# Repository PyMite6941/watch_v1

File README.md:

# Watch V1

A see-through, build-it-yourself wrist watch made as a gift for STEM teachers. An ESP32-C3 SuperMini drives a four-digit LED display, an RGB LED and a vibration motor inside a clear printed case. Every watch is set up for its owner with **Watch Studio**, a tiny desktop app for Windows and macOS — no programming — and takes plug-in **packs** for extra abilities (a weather sensor for biology, a microphone tuner for music).

| | |
|---|---|
| Size | 62.8 × 48.8 × 25.3 mm case, 22 mm strap |
| Display | 0.56" four-digit seven-segment, auto-dimming |
| Battery | 150 mAh Li-Po, charged through its own USB socket |
| Radios | Wi-Fi (time sync), Bluetooth LE (setup), ESP-NOW (watch-to-watch) |
| Controls | Two buttons: MODE and SET |
| Expansion | 2×3 accessory socket on the face (I²C, switched power, analogue in) |

## Where things stand

| Part | State |
|---|---|
| Circuit (`hardware/scripts/design.py`) | Done, revision 5. Schematic generated, electrical rules check passes with 0 findings. |
| PCB | All 49 parts placed and checked; an automatic audit confirms every connection against the parts' pinouts. Routing and Gerbers are made in the cloud by a GitHub workflow, so builders never run a router — see [`hardware/README.md`](hardware/README.md). |
| Enclosure | Modelled; STL files exported in `enclosure/stl/`. Not yet test-printed against a real board. |
| Firmware 2.2.0 | Complete and compiles for the ESP32-C3 (custom apps, file space, live data, I²C bridge, weather). **Not yet run on hardware** — expect a debugging session on the first assembled watch. |
| Watch Studio app | Done; tested against its built-in demo watch. Installers for Windows (tested) and macOS (not yet tried on a Mac) in [`installer/`](installer/README.md). Needs a real watch to be tested over USB and Bluetooth. |

The list of what is left is kept outside the repository.

## Start here

| You want to… | Read |
|---|---|
| Use a finished watch | [`docs/USER_GUIDE.md`](docs/USER_GUIDE.md) |
| Install the app | Download from [Releases](https://github.com/PyMite6941/watch_v1/releases) — details in [`installer/README.md`](installer/README.md) |
| Use the app without installing it | Host it on the web with Vercel, or run it as a Java app — [`docs/APP_HOSTING.md`](docs/APP_HOSTING.md) |
| Set one up (Wi-Fi, screens, bells, custom apps) | [`docs/CONFIGURATION.md`](docs/CONFIGURATION.md) |
| Build one | [`docs/BUILD_GUIDE.md`](docs/BUILD_GUIDE.md), parts in [`docs/BOM.md`](docs/BOM.md) |
| Order boards and cases | [`docs/ORDERING.md`](docs/ORDERING.md); what each add-on costs: [`docs/COSTS.md`](docs/COSTS.md) |
| Add sensors or other hardware | [`docs/ADDONS.md`](docs/ADDONS.md); pack boards and costs in [`hardware/addons/`](hardware/addons/README.md) |
| See what it could do for each subject | [`docs/IDEAS.md`](docs/IDEAS.md) |
| Make one for a particular person (biology, computer science, band, calculus, youth group) | [`kits/`](kits/README.md): preset, pack, engraved case and printed stand for each |
| Change the circuit or board | [`hardware/README.md`](hardware/README.md) |

## What it does

- **Clock**: time, seconds, date, battery level. Keeps time with a DS3231 clock chip and corrects itself over Wi-Fi.
- **Weather** (over Wi-Fi): temperature, sky, high/low, chance of rain, sunrise/sunset and air quality for a place you choose.
- **Classroom tools**: stopwatch, countdown timer, tally counter, dice, bell schedule with a countdown to the next bell, metronome.
- **Packs** (plug into the accessory socket): temperature, humidity and air pressure with a sample log you download as a spreadsheet; an instrument tuner.
- **Watch-to-watch**: watches in the same group can see each other, buzz each other and share the time, with no router.
- **Custom apps**: step timers, random name pickers, countdowns and messages, made in Watch Studio and stored on the watch.
- **Personal**: each owner chooses which screens appear and in what order, brightness, time zone, 12/24-hour, bells, and more.

Battery life comes from being asleep: the watch wakes when a button is pressed, shows a screen for a few seconds and sleeps again. It also wakes on its own for a bell, a finished timer, a log sample or a time sync.

## Repository layout

```
firmware/watch_v1/     Arduino sketch (one file per feature; start with watch_v1.ino)
app/                   Watch Studio, the companion app (one page: index.html)
installer/             Windows and macOS installers for it; build.py makes dist/*.zip
java-app/              the same app as a Java program; build.py makes dist/WatchStudio.jar
vercel.json            serves app/ as a web site on Vercel
hardware/scripts/      design.py is the circuit; the other scripts generate KiCad files from it
hardware/kicad/        generated KiCad 10 project (schematic, board, libraries)
hardware/addons/       add-on boards: the Pack Base (sensor packs) and the Screen Pack (OLED)
tools/oled/            OLED icons, pictures, clock faces, built-in designs and the C/JS parity test
enclosure/             OpenSCAD model (case with optional engraving, accessories) and exported STL files
kits/                  ready-made setups for one person each: preset, pack, case pattern, ideas
docs/                  guides
```

## Licence

MIT — see [`LICENSE`](LICENSE). Keep the copyright notice in copies.

Pull requests are welcome when written by a person; automated or bot-generated pull requests are not accepted.

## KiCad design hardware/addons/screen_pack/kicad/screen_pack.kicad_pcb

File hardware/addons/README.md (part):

# Add-on packs: hardware

Plug-in boards for the watch's accessory socket. What the socket is and what it can do is in [docs/ADDONS.md](../../docs/ADDONS.md); this folder holds the boards and the plan for making packs cheaply.

**Status: sketch.** The Pack Base and Screen Pack boards below are designed and routed. Both pass KiCad's design-rule check (0 problems), their schematics pass the electrical-rule check, and their factory files are exported. Neither has been ordered, built or plugged into a watch.

| Folder / file | What it is |
|---|---|
| `pack_base/gen_pack_base.py` | Generates the Pack Base board, checks it, and with `--fab` exports the factory files |
| `pack_base/kicad/pack_base.kicad_pcb` | The board, placed and routed. Open it in KiCad 10 |
| `pack_base/gen_pack_base_sch.py` | Generates the schematic from the same parts table (any Python 3) |
| `pack_base/kicad/pack_base.kicad_sch` | The schematic: 0 electrical-rule findings, and its nets match the board's |
| `pack_base/fab/pack_base_gerbers.zip` | Upload this to the PCB factory |
| `pack_base/render_top.png`, `render_bottom.png` | Pictures of both sides |
| `screen_pack/gen_screen_pack.py`, `gen_screen_pack_sch.py` | The same for the Screen Pack (an OLED strip that lies on the lid). Reads its shared numbers from `enclosure/enclosure.scad` |
| `screen_pack/kicad/` | Its board and schematic |
| `screen_pack/fab/screen_pack_gerbers.zip` | Upload this to the PCB factory |
| `screen_pack/render_top.png`, `render_bottom.png` | Pictures of both sides |

## The idea: one board for every pack

Instead of a different board per pack, every pack is the same **Pack Base** with a cheap ready-made sensor board soldered on top. This keeps costs down three ways:

1. **One design, one order.** PCB factories charge per design. Five Pack Bases come in the same minimum order as one, so there is one order to pay for instead of one per pack.
2. **Order it in the same basket as the watch board,** so they ship together. Shipping usually costs more than the boards themselves.
3. **The sensors are mass-produced breakout boards** that cost little each (see the catalogue). Nothing on the Pack Base itself costs more than a few cents apart from the optional Qwiic socket.

It also makes the gift more versatile, because the Pack Base takes three kinds of add-on:

- **Breakout row (J2):** 6 holes in the order most cheap I²C boards use: `V G SCL SDA` and two spare holes. A GY-BME280 solders straight in, and its two extra pins land in the spare holes. BH1750, GY-521 (MPU6050) and most AHT20 boards start with the same 4 pins. Match the printed labels, not the pin count.
- **Microphone row (J3):** `G`, `X` (AUX) and `A` (AIN), for a MAX4466 or MAX9814 board. Power comes from AUX, so the microphone is off while the watch sleeps.
- **Qwiic / STEMMA QT socket (J5):** the 4-pin plug used by hundreds of SparkFun and Adafruit sensors, and by cheap copies of them. With it, a teacher can buy a new sensor later and plug it in with a cable, with no soldering. Several Qwiic sensors can chain one after another. Leave the socket off to save money; the board works without it.

Every I²C sensor shows up in Watch Studio's *Lab › Scan the socket* the moment it is plugged in, even before the firmware knows how to read it. That makes "what is on the bus?" a lesson on its own.

## The Pack Base board

20 × 18.6 mm, 2 layers, all through-hole except the optional Qwiic socket.

```
   top side, pack plugged in             underneath
   ┌──────── [Qwiic] ────────┐           ┌─────────────────────────┐
   │  V  G  CL DA  -  -      │  J2       │  "AWAY FROM DISPLAY"    │
   │ [3|·|X]            ○ G  │  JP1, J3  │                         │
   │                    ○ X  │           │   2x3 male header (J1)  │
   │      ● 1  ○ 3  ○ 5      │           │   plastic on this side  │
   └──────○ 2──○ 4──○ 6─○ A──┘           └─────────────────────────┘
          edge nearest the display
```

- **J1** is a standard straight 2×3 male header, plastic strip underneath, soldered on top. Its pins are exactly over the watch's socket. The generator checks this against the watch board's coordinates every time it runs.
- **The bottom edge is 1.3 mm below the lower pin row,** so the pack stops short of the display window (it starts 1.8 mm below). The rest of the board sticks out past the top edge of the watch.
- **JP1 sensor power:**
  - The pads come joined between `3` and the centre, so sensors are always powered from 3V3.
  - To power them only while the watch is awake, cut that join with a knife and put a blob of solder between the centre and `X` (AUX).
  - See *Battery life* below before relying on this.
- **Pin 1** has a square pad and a printed `1` on both sides, plus "PIN 1 = LID NOTCH" underneath.

To rebuild after a change:

```bash
"%LOCALAPPDATA%\Programs\KiCad\10.0\bin\python.exe" hardware/addons/pack_base/gen_pack_base.py --fab
```

It prints its placement checks and the design-rule result. It only writes the factory files when both are clean.

The schematic comes from the same parts table, so after changing a part's nets also run `python hardware/addons/pack_base/gen_pack_base_sch.py`.

### Ordering

Upload `pack_base/fab/pack_base_gerbers.zip`. The defaults are right: 2 layers, 1.6 mm, any colour, HASL (lead-free if offered). Add it to the same basket as the watch board.

The minimum order is usually 5 boards. For more, choose the factory's own panelising (at JLCPCB, "Panel by JLCPCB", 2 × 2) to get 4 boards per panel, which is 20 from the minimum order. Check what it adds to the price; it is usually small.

### Building a pack on it

1. Solder J1 (the 2×3 header) first: plastic underneath, solder on top, trim the pins flush on top.
2. Sensor board: push its own header pins through J2 from the top and solder underneath. Lay the sensor flat over the Pack Base, body towards the display end, with its header's plastic as the spacer. Do not stand it upright; that would make it very tall on a wrist.
3. Microphone board: same at J3, matching `G` / `X` / `A` to the board's GND / VCC / OUT.
4. Qwiic socket, if wanted: solder it last. It is surface-mount with pins 1 mm apart. That is doable with flux and a fine tip, or the PCB factory can fit it.
5. Before the first plug-in, measure resistance between J1 pins 1 and 2: it must not be near 0 Ω.

## The Screen Pack board

A strip that holds a 0.91" I²C OLED **flat on top of the watch**, along the edge above the 7-segment digits. It plugs straight down into the watch's accessory socket through the lid's opening, and the printed **screen clip** snaps over it to hold everything down. What the screen shows, and how teachers design their own screens, is in [docs/OLED_SCREENS.md](../../docs/OLED_SCREENS.md).

r2: 40.5 × 10.9 mm, 2 layers, all through-hole: one 2×3 header and two columns of holes for the module's own pins.

```
 seen from above, on the watch (the case's top edge is the dashed line)

   ┌─A─B────────────────────────────────────────┐   strip, overhanging the case edge
   │ ○ ○ DA DA                                   │
 - │ ○ ○ CL CL - - - - - - - - - - - - - - - - - │ - case edge
   │ ○ ○ V  G                     J1 underneath: │
   │ ○ ○ G  V                     ● ○ ○  in the  │
   └─────────────────────────────── ○ ○ ○ socket ┘
          the 7-segment display window starts 0.2 mm below this edge

   the OLED lies over the whole strip: pins on the left, glass facing up
```

- **Everything is mapped from one set of numbers.** The strip's outline, the module's size and where it sits are written once in [`enclosure/enclosure.scad`](../../enclosure/enclosure.scad) (the *Screen Pack r2* block). `gen_screen_pack.py` reads those lines to build the board, and the case model uses the same lines for the screen clip and the lid's pin pocket. Each side checks itself every time it runs:
  - the generator checks that J1's pins sit exactly over the watch's socket J4 (taken from the watch board's coordinates), that J1's plastic fits through the lid's opening with 0.2 mm to spare, that the strip stops short of the display window, that the module stays inside the lid's length in either column and stops 1.9 mm short of the digits, and that both columns have the right pin order;
  - `enclosure.scad` asserts that the strip and the pin pocket stay out of the display window, that the clip's end blocks and front wall keep 0.4 mm or more from the strip and the module in either column, that its plate stays above the glass, that its arms keep clear of both USB openings, that its hooks miss the screw counterbores, that the rib grooves are shallow enough for the wall and sit on the flat part of it, and that the hook still has at least 0.2 mm of height tolerance.
- **Two columns, because cheap OLED boards come with two pin orders.** Column A is for modules labelled `GND VCC SCL SDA` (most 0.91" boards), column B for `VCC GND SCL SDA`. Solder the module into the one column whose letters match its own. Column B is one pin pitch (2.54 mm) to the right, so the module simply sits 2.54 mm further right; the clip covers both positions.
- **Why on top, and not under the lid:** the lid's top strip is the only free surface the socket reaches. Under the lid along this edge are C1, C4 and the standing resistors R1–R8, R22 and R23, so the clip does not reach under the lid at all. It goes round the outside of the case instead (next section).
- The OLED runs from the watch's 3V3. AUX and AIN (pins 5 and 6) are not connected.
- **Measured from photos, not from a module in hand.** The module's 38 × 12 mm outline is from sellers' drawings ([ProtoSupplies](https://protosupplies.com/product/oled-0-91-128x32-i2c-white-display/), [ThingBits](https://thingbits.in/products/0-91-inch-oled-128x32-display-board-with-i2c)). Its 2.7 mm thickness is DFRobot's figure for its DFR0648. The pin row's position (1.7 mm in from the left edge, centred across the width) and where the lit area sits were read off a seller's labelled photo. **Measure your module before ordering many**, then change the numbers in `enclosure.scad` and rebuild both: one edit moves the board and the clip together.
- A 0.96" 128×64 module is square, more than twice as tall as the 0.91" one, so it would cover the digits. It does not fit this strip. Use it on a cable with the Pack Base ([ADDONS.md](../../docs/ADDONS.md)).

To rebuild after a change (the board generator reads `enclosure.scad`, so re-export the STLs too):

```bash
"%LOCALAPPDATA%\Programs\KiCad\10.0\bin\python.exe" hardware/addons/screen_pack/gen_screen_pack.py --fab
python hardware/addons/screen_pack/gen_screen_pack_sch.py
openscad -D "part=\"screen_clip\"" -o enclosure/stl/screen_clip.stl enclosure/enclosure.scad
openscad -D "part=\"lid\""  -o enclosure/stl/lid.stl  enclosure/enclosure.scad
openscad -D "part=\"base\"" -o enclosure/stl/base.stl enclosure/enclosure.scad
openscad -D "part=\"screen_clip_test\"" -o enclosure/stl/screen_clip_test.stl enclosure/enclosure.scad
```

`openscad -D "part=\"screen_assembly\"" enclosure/enclosure.scad` shows the strip, the module and the clip in place on the case.

Order it like the Pack Base: upload `screen_pack/fab/screen_pack_gerbers.zip` with the default settings, ideally in the same basket as the watch boards.

### The screen clip

It holds the strip and the OLED on the watch, and it is braced on the case from **both sides, the top and the bottom**:

- **Two side arms** run down the case's left and right ends (the short sides), 0.1 mm off the wall, and each ends in a **hook under the case floor**. They sit in the top 15 mm of each end, clear of the USB-C and charger openings, the strap lugs and the screw heads.
- The hooks' catch face slopes at **18°**, and each hook starts 0.2 mm into the floor. So when the clip is on, both arms are bent outward a little and their spring **pulls the clip down onto the lid**: it does not rattle, and a case a little taller or shorter than the model still fits. The model's window is **0.2 mm shorter to 0.29 mm taller** than `case_h`: down to 0.2 mm shorter the clip stays tight (any shorter and it has a little play), and more than 0.29 mm taller the hooks no longer reach under. Worked out for PETG: about 1 N of spring per arm when fitted, about 2.5 N per arm to push it on, and roughly 10–30 N per arm to pull it straight off, depending on friction: far more than it meets by accident. These are worked out, not measured.
- **Two end blocks** rest on the lid top either side of the strip (the top brace), and their front faces sit against the case's front face.
- A **rib** inside each arm runs in a vertical **groove** in each end wall (base and lid), so the clip cannot slide forward or back, and it guides the clip straight down while you push.
- The **top plate** stays 0.6 mm above the OLED glass, with a window over the lit area that is open at the back: nothing presses on the module or on the thin skin over the 7-segment digits. The strip itself is held by J1 in the socket; the plate only stops it lifting.
- Nothing goes under the strip, so the clip goes on and off with the screen in place.

**One print, so measure first.** Printed cases come out a little off the model, and the hooks need the real height:

1. Screw the lid on the printed case. With calipers, measure from the **bottom face to the lid's top face**, at the left and at the right end, next to the screen edge. Use the average of the two.
2. Put it in `measured_case_h` at the top of `enclosure.scad` (0 means the model's 25.3 mm). If you have the screen already, you can also measure the glass's height above the lid and put it in `measured_glass_h`.
3. Export and print **`screen_clip_test.stl`** first: the left end of the clip only (arm, hook, rib, block), 2.3 cm³. It should slide down with the rib in its groove, click under the floor, and sit on the lid with no rattle. If it will not click under the floor, raise `measured_case_h` by 0.1; if it rattles up and down, lower it by 0.1. Then print the test piece again.
4. Then export and print `screen_clip.stl`.

**Printing it:** the STL is already lying on its **front face** (the flat face with the long front wall); print it that way, PETG, 0.2 mm layers, no supports, at least 3 walls. Every part of it grows straight up from the bed, and the arms bend along the layers rather than across them, so they do not snap at a layer line. PLA works, but it is stiffer and more brittle: it will be harder to push on and may crack if taken off often.

### Building it

You need the strip, a 0.91" OLED module (with the 4-pin male header it comes with), a 2×3 male header, and the screen clip, printed after measuring your case (see *The screen clip* above). The case must be the current `base.stl` and `lid.stl`, which have the rib grooves in both end walls and the pin pocket.

1. **J1 first:** a 2×3 male header, plastic **underneath**, the long pins pointing down. Solder on top and trim flush: the module lies over these joints.
2. Read the four letters on your OLED's pins. They pick the column: **A** if the module reads `GND VCC SCL SDA`, **B** if `VCC GND SCL SDA`.
3. Solder the 4-pin header into the module first (sellers ship it loose). Then put its long pins down through that column, **glass facing up, pins at the left-hand end** (the silkscreen says so). The header's plastic sits on the strip and holds the module 2.5 mm above it.
4. Solder the four pins underneath and **trim them to about 1 mm**. They sit in a 1 mm pocket in the lid; longer stubs stop the strip lying flat.
5. Before the first plug-in, measure between J1 pins 1 and 2: it must not be near 0 Ω.
6. With the watch off, push J1 down into the socket through the lid's opening (pin 1, the square pad, goes to the notched corner). The strip lies flat on the lid, overhanging the top edge.
7. Fit the screen clip from above: line the ribs inside its arms up with the grooves in the case's end walls, then press straight down until both hooks click under the floor. To take it off, pull one arm's hook outward with a fingernail and lift that end, then the other.
8. If the picture is upside down, tick *OLED picture upside down* in Watch Studio's settings.
9. In the desk stand, stand the watch with the screen edge at the **top**: the clip sticks out 4.5 mm past the case's front, 8.6 mm above the lid and about 2.2 mm below the floor at both ends, so it does not fit in the stand's trough. The hooks sit outside the stand's 44 mm back, so the watch still leans flat.
4. Plug the OLED in, set *Settings › OLED screen* to its size, and press *Screens › Show the watch's OLED now*.

## Catalogue

"Works now" means the firmware already has a screen for it. "Scan only" means it shows up in Watch Studio's I²C scan, but it needs a small driver before the watch can display its readings. The price bands are rough guesses for cheap marketplace listings, not checked quotes, so compare before buying:

- **$**: under about $2
- **$$**: about $2–6
- **$$$**: $10 and up

| Pack | Module | Firmware | Cost | Good for |
|---|---|---|---|---|
| Environment | GY-BME280 (3.3 V version) | **Works now:** temperature, humidity, pressure, logging | $$ | Biology, environmental science, chemistry; pressure gives altitude, e.g. climbing stairs |
| Environment, no humidity | GY-BMP280 | **Works now:** temperature, pressure | $ | Same, cheaper. Many "BME280" listings actually ship this chip. The watch tells which one it is (no humidity screen) |
| Sound | MAX4466 board (MAX9814 also works) | **Works now:** tuner | $ | Music |
| Humidity, cheaper | AHT20 (often sold on one board with a BMP280) | Scan only (the BMP280 half works now) | $ | Environment pack at the lowest price. **Best next driver:** a few dozen lines |
| Light | BH1750 | Scan only | $ | Photosynthesis, inverse-square law. **Easy driver** |
| Motion | GY-521 (MPU6050); tie AD0 high, address `0x69` | Scan only | $ | Physics: pendulums, acceleration, step counting |
| Distance | VL53L0X | Scan only | $$ | Physics: motion graphs |
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
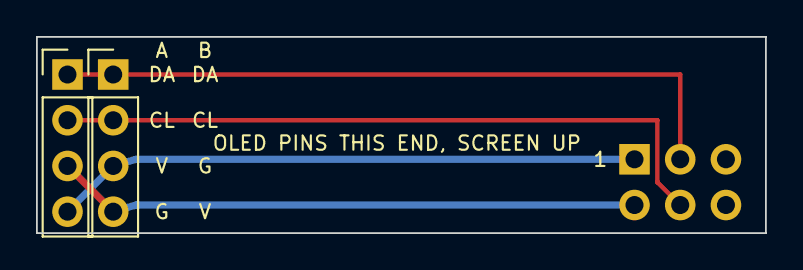
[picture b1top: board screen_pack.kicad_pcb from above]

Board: 2 copper layers, 40.5 x 10.9 mm, 3 parts (1 on the bottom side), 4 nets.

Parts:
J1: PinHeader_2x03_P2.54mm_Vertical
J2, J3: PinHeader_1x04_P2.54mm_Vertical

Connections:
+3V3: J1.2, J2.3, J3.4
GND: J1.1, J2.4, J3.3
SCL: J1.4, J2.2, J3.2
SDA: J1.3, J2.1, J3.1

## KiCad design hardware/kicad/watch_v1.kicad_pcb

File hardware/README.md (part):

# Hardware

The circuit is described once, in code, and everything else is generated from it.

```
scripts/design.py      THE circuit: every part, its value, footprint and which net each pin is on
scripts/gen_sch.py     -> kicad/watch_v1.kicad_sch   (any Python 3)
scripts/gen_pcb.py     -> kicad/watch_v1.kicad_pcb   (KiCad's own Python: needs the pcbnew module)
scripts/check_wiring.py  audits the generated schematic and board against datasheet pinouts
scripts/freeroute.py   -> kicad/watch_v1.ses         (Freerouting; run for you by the cloud workflow)
scripts/route.py       -> kicad/watch_v1.routes.json (any Python 3; experimental autorouter)
scripts/export_fab.py  -> fab/watch_v1_gerbers.zip   (checks the board first)
kicad/                 the generated KiCad 10 project - open watch_v1.kicad_pro
addons/                add-on packs: the Pack Base board (routed, design-rule clean) and the pack plan
```

**Edit `design.py`, not the KiCad files** — anything changed by hand in the schematic or in the footprint positions is overwritten the next time the scripts run. Tracks are the exception: see below.

## Current state — revision 6

| Check | Result |
|---|---|
| Schematic electrical rules (ERC) | 0 findings |
| Placement self-checks (display orientation, USB end, parts inside the outline) | all pass |
| Wiring audit (`check_wiring.py`) | 55 checks against datasheet pinouts and the firmware's pin table, all pass |
| Board against schematic | 0 differences |
| Design rules (DRC) | clean apart from routing, which the cloud workflow does (see *Routing*) |

The board is placed; routing and the Gerbers come from the cloud workflow below, so nobody has to run a router.

## Finding pin 1 — on the drawings and on the parts

Every part that can go in the wrong way round is marked in three places: a note on the schematic next to its block, printing on the board, and (for the accessory socket) the case.

| Part | On the real part | On the board | Counting |
|---|---|---|---|
| U1 SuperMini | USB-C socket at one end; pad names printed on it | Outline with the USB end drawn and "USB-C THIS END"; each pad's name printed (5V, GND, 3V3, 4, 3, 2, 1, 0 / 5, 6, 7, 8, 9, 10, 20, 21); pad 1 is square | Component side up, USB at the top: pads 1–8 down the left, 9–16 up the right. Pad 1 = GPIO5, pad 16 = 5V. |
| U2, U3 74HC595 | Notch (and often a dot) at the pin 1 end | Notch in the outline; corner numbers **1, 8, 9, 16** printed beside the pads; pad 1 square | Notch up: 1–8 down the left, 9–16 up the right |
| DS1 display | Decimal points along the bottom edge | "DP THIS EDGE"; corner pins **1, 6, 7, 12** printed | From the front: 1–6 left to right along the bottom, 7–12 right to left along the top |
| Q1–Q5 | Flat face | Outline with the flat; **EBC** printed under each | Flat towards you, legs down: E, B, C |
| D3 RGB LED | Longest leg = cathode | **RKGB** printed under it | Left to right: red, cathode, green, blue |
| D1, D2 | Band = cathode | "K" at the cathode pad | |
| J4 accessory socket | — | **1** printed beside pin 1; square pad on the back | Top row 1 GND, 3 SDA, 5 AUX; bottom row 2 3V3, 4 SCL, 6 AIN. The lid opening has a round notch at the pin 1 corner. |
| J1, J2, J3 wire pads | — | Every pad named: 3V3 SDA SCL NC GND / G BAT CHG / MOTOR + − | |

Parts on the back of the board (U1, U2, U3) are drawn mirrored in KiCad's front view, as they must be; flip the view (`View → Flip Board View`) to see them as you will when soldering.

```
   U2 / U3  (74HC595)                  DS1 from the front               Q1-Q5, flat face to you
      ┌──╮╭──┐                    12  11  10   9   8   7                    ┌─────────┐
  QB 1│  ╰╯  │16 VCC             ┌──────────────────────┐                   │         │
  QC 2│      │15 QA              │  8.   8.   8.   8.   │                   └─┬──┬──┬─┘
  QD 3│      │14 SER             └──────────────────────┘                     E  B  C
  QE 4│      │13 /OE               1   2   3   4   5   6
  QF 5│      │12 RCLK                                                   J4 from the front
  QG 6│      │11 SRCLK           D3, legs down                          ╭ notch
  QH 7│      │10 /SRCLR           R  K  G  B                            ● 1 GND  3 SDA  5 AUX
 GND 8│      │9  QH'                 └ longest                            2 3V3  4 SCL  6 AIN
      └──────┘
```

## Reading the schematic

The sheet is drawn as an annotated netlist: every pin has a short stub and a label, and **pins with the same label are connected**. There are no long wires to follow. Each block has a title (MCU, segment driver, display, power…).

## The circuit in one paragraph

A Li-Po cell feeds the SuperMini's 5 V pin through Schottky diode D1; the SuperMini's own regulator makes 3.3 V for everything. The cell is charged by a separate TP4056 board through *its* USB socket, which is deliberately not connected to the SuperMini's USB — that port stays free for data. Two 74HC595 shift registers turn four processor pins into sixteen outputs: U2 drives the eight display segments through 220 Ω resistors; U3 switches the four digits (through NPN transistors Q1–Q4), the three colours of the RGB LED, and the vibration motor (through Q5). The shift registers' output-enable pin is driven with PWM for brightness and pulled high by R17 so nothing lights before the firmware starts. A DS3231 keeps time on the I²C bus, which also goes to accessory socket J4. R18/R19 halve the battery voltage for measurement; C4 couples the accessory socket's audio input onto that same pin. The light sensor divider (R21/R20) and the socket's AUX pin are powered from a processor pin so they cost nothing in sleep.

| GPIO | Net | Purpose |
|---|---|---|
| 0 | VBAT_SENSE | Battery ÷ 2 (ADC); accessory audio rides on it through C4 |
| 1 | LDR_SENSE | Light sensor (ADC) |
| 2 | — | Strapping pin, left unconnected on purpose |
| 3, 4 | BTN_MODE, BTN_SET | Buttons to ground; both can wake the chip from deep sleep |
| 5 | CHRG | Charger "charging" signal, low = charging |
| 6, 7, 10 | SR_DATA, SR_CLK, SR_LATCH | Shift registers |
| 8, 9 | SDA, SCL | I²C: clock chip, accessory socket; pulled up by R22, R23 |
| 20 | SR_OE | Shift-register output enable (PWM brightness) |
| 21 | LDR_PWR | Switched 3.3 V: light sensor and accessory AUX pin |

Every pin the SuperMini exposes is used. That is why the accessory socket shares pins rather than getting its own.

## Regenerating

Windows paths shown; the KiCad Python lives inside the KiCad install.

```bash
cd hardware/scripts
python gen_sch.py
"%LOCALAPPDATA%\Programs\KiCad\10.0\bin\python.exe" gen_pcb.py
python check_wiring.py
```

`check_wiring.py` is the independent audit. It ignores `design.py`, takes the netlist KiCad extracts from the schematic and the pad nets of the board, and checks them against pinouts written out from the datasheets and against `firmware/watch_v1/config.h` — for example "segment A: U2 output QA (pin 15) → R1 → display pin 11". Run it after every change; it ends with `ALL CHECKS PASSED` or names what is wrong.

What it cannot check: that the parts you buy match those datasheets. The three that vary between sellers are the display (must be common cathode with the 5641AS/5643AS pinout), the transistors (must be E-B-C) and the RGB LED (must be common cathode, leg order R-K-G-B). Test each with a multimeter's diode range before soldering.

Set `KICAD_SYMBOL_DIR` / `KICAD_FOOTPRINT_DIR` if KiCad is installed somewhere else. `gen_pcb.py` prints a line per placement check and fails if one does not pass.

To move a part, change its entry in `PLACE` in `gen_pcb.py` (millimetres from the board's top-left corner, looking at the display side). The enclosure reads the same coordinates — if the display, buttons, LED, light sensor, accessory socket or USB end move, update the matching numbers at the top of `enclosure/enclosure.scad`.

## Routing — done in the cloud

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
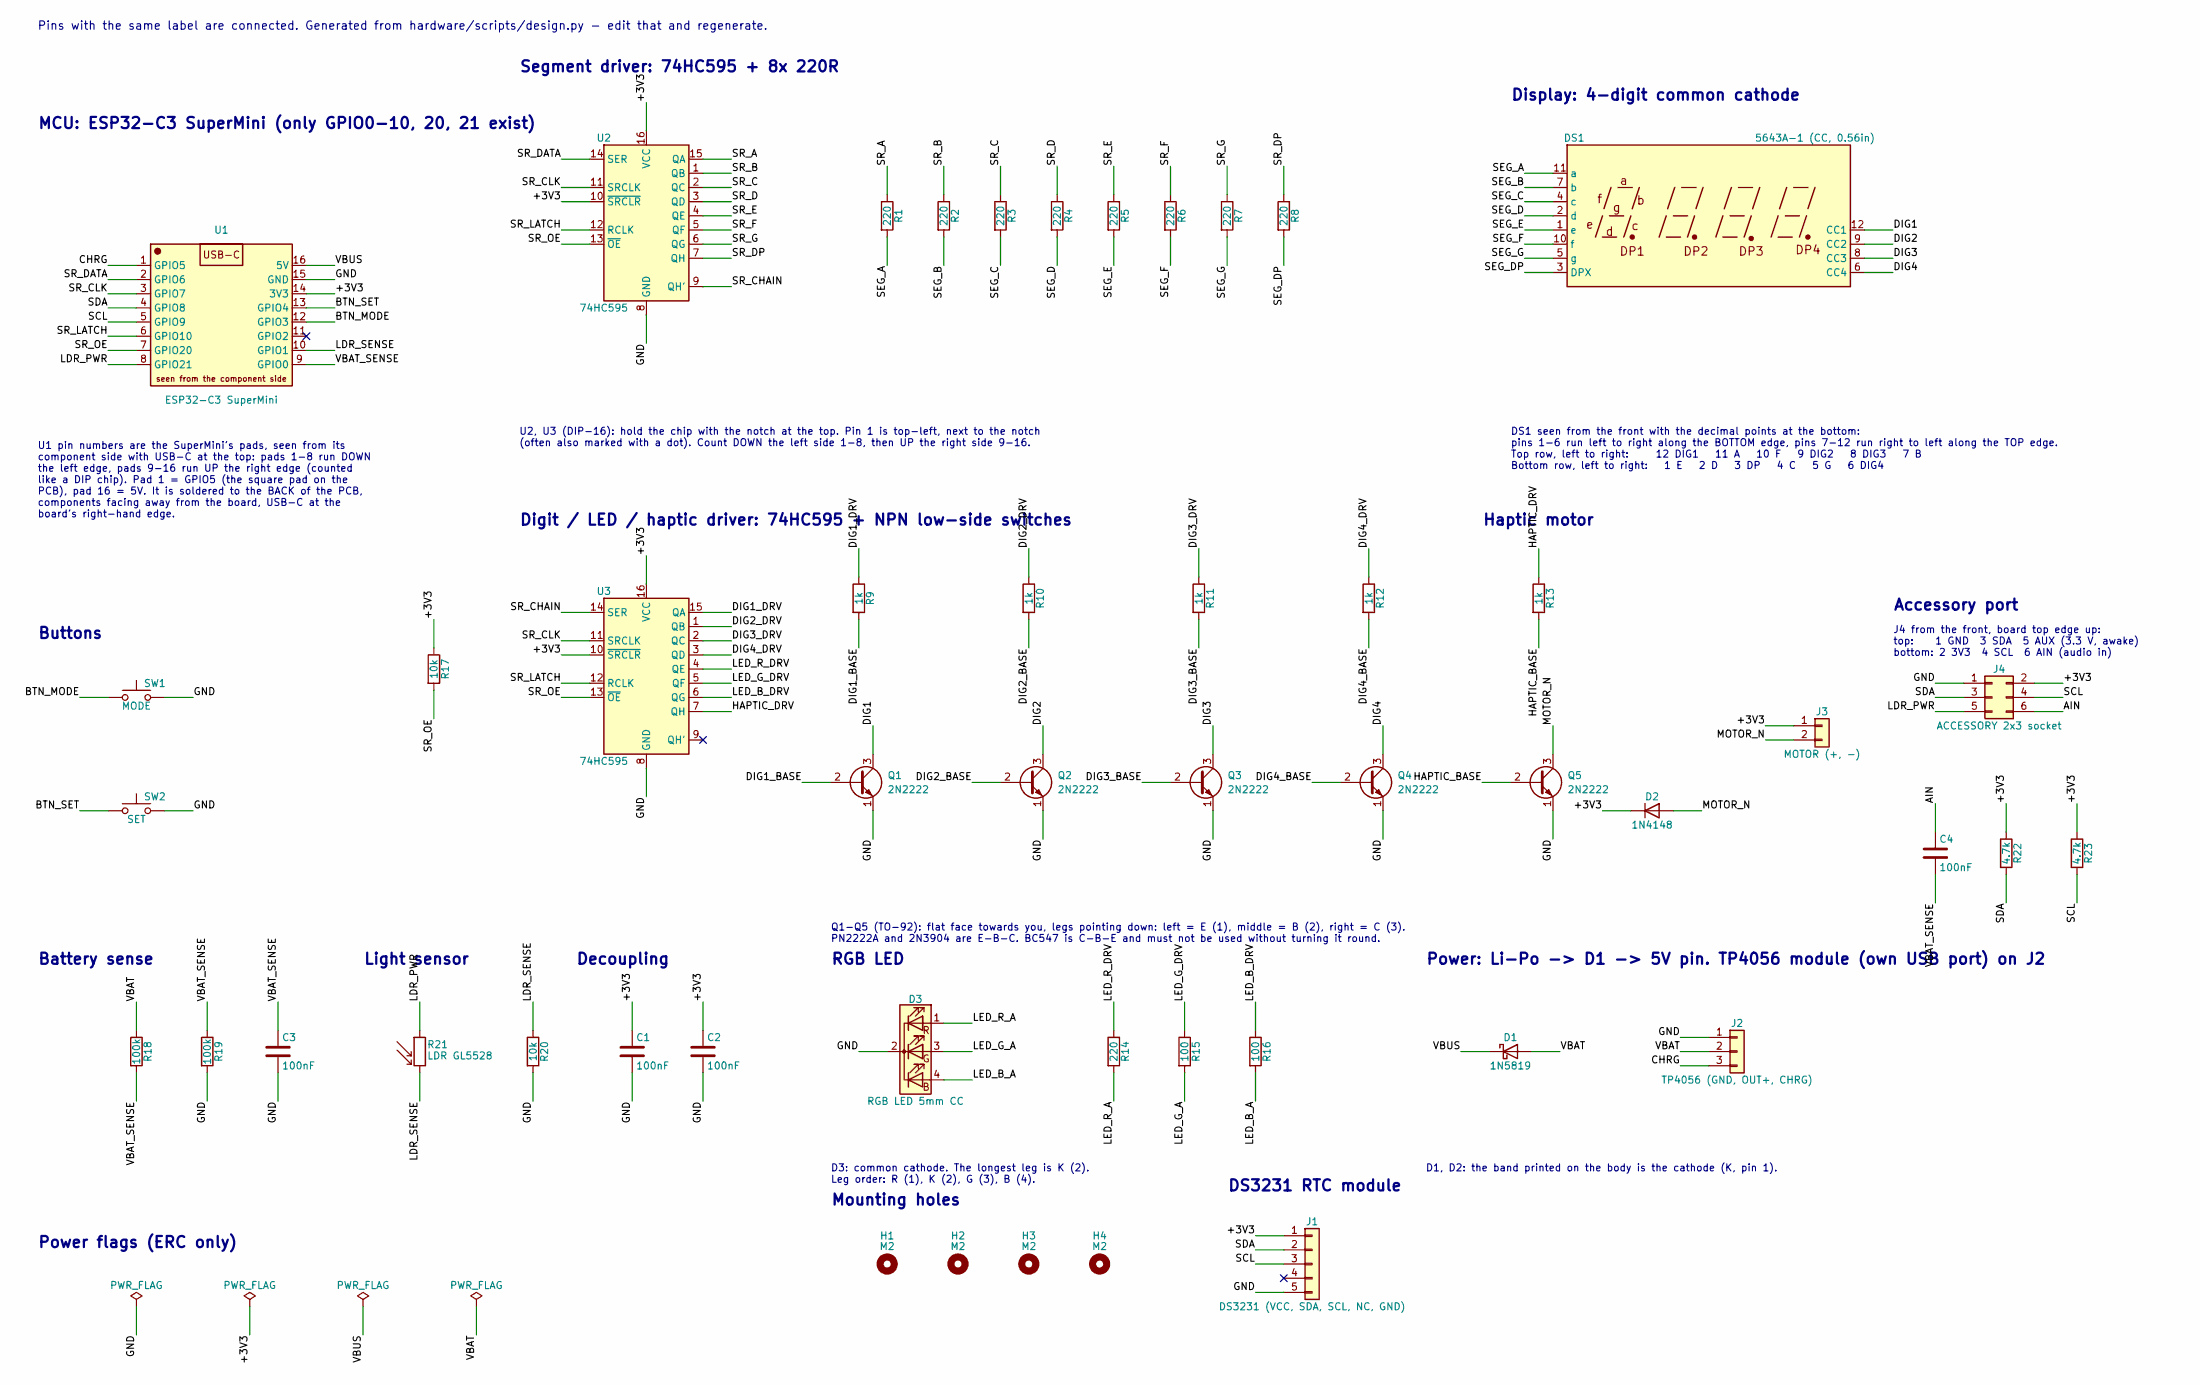
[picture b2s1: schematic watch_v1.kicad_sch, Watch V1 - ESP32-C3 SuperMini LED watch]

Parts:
C1, C2, C3, C4: 100nF; C_Disc_D3.0mm_W1.6mm_P2.50mm
D1: 1N5819; D_DO-41_SOD81_P2.54mm_Vertical_AnodeUp
D2: 1N4148; D_DO-35_SOD27_P2.54mm_Vertical_AnodeUp
D3: RGB LED 5mm CC; LED_D5.0mm-4_RGB
DS1: 5643A-1 (CC, 0.56in); CC56-12GWA
H1, H2, H3, H4: M2; MountingHole_2.2mm_M2
J1: DS3231 (VCC, SDA, SCL, NC, GND); PinHeader_1x05_P2.54mm_Vertical
J2: TP4056 (GND, OUT+, CHRG); PinHeader_1x03_P2.54mm_Vertical
J3: MOTOR (+, -); PinHeader_1x02_P2.54mm_Vertical
J4: ACCESSORY 2x3 socket; PinSocket_2x03_P2.54mm_Vertical
Q1, Q2, Q3, Q4, Q5: 2N2222; TO-92_Inline
R1, R2, R3, R4, R5, R6, R7, R8, R14: 220; R_Axial_DIN0207_L6.3mm_D2.5mm_P2.54mm_Vertical
R9, R10, R11, R12, R13: 1k; R_Axial_DIN0207_L6.3mm_D2.5mm_P2.54mm_Vertical
R15, R16: 100; R_Axial_DIN0207_L6.3mm_D2.5mm_P2.54mm_Vertical
R17, R20: 10k; R_Axial_DIN0207_L6.3mm_D2.5mm_P2.54mm_Vertical
R18, R19: 100k; R_Axial_DIN0207_L6.3mm_D2.5mm_P2.54mm_Vertical
R21: LDR GL5528; R_LDR_5.1x4.3mm_P3.4mm_Vertical
R22, R23: 4.7k; R_Axial_DIN0207_L6.3mm_D2.5mm_P2.54mm_Vertical
SW1: MODE; SW_PUSH_6mm_H13mm
SW2: SET; SW_PUSH_6mm_H13mm
U1: ESP32-C3 SuperMini; ESP32-C3_SuperMini
U2, U3: 74HC595; DIP-16_W7.62mm

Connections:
/+3V3: C1.1, C2.1, D2.1 (K), J1.1, J3.1, J4.2, R17.1, R22.1, R23.1, U1.14 (3V3), U2.10 (~SRCLR), U2.16 (VCC), U3.10 (~SRCLR), U3.16 (VCC)
/AIN: C4.1, J4.6
/BTN_MODE: SW1.1, U1.12 (GPIO3)
/BTN_SET: SW2.1, U1.13 (GPIO4)
/CHRG: J2.3, U1.1 (GPIO5)
/DIG1: DS1.12 (CC1), Q1.3 (C)
/DIG1_BASE: Q1.2 (B), R9.2
/DIG1_DRV: R9.1, U3.15 (QA)
/DIG2: DS1.9 (CC2), Q2.3 (C)
/DIG2_BASE: Q2.2 (B), R10.2
/DIG2_DRV: R10.1, U3.1 (QB)
/DIG3: DS1.8 (CC3), Q3.3 (C)
/DIG3_BASE: Q3.2 (B), R11.2
/DIG3_DRV: R11.1, U3.2 (QC)
/DIG4: DS1.6 (CC4), Q4.3 (C)
/DIG4_BASE: Q4.2 (B), R12.2
/DIG4_DRV: R12.1, U3.3 (QD)
/GND: C1.2, C2.2, C3.2, D3.2 (K), J1.5, J2.1, J4.1, Q1.1 (E), Q2.1 (E), Q3.1 (E), Q4.1 (E), Q5.1 (E), R19.2, R20.2, SW1.2, SW2.2, U1.15 (GND), U2.8 (GND), U3.8 (GND)
/HAPTIC_BASE: Q5.2 (B), R13.2
/HAPTIC_DRV: R13.1, U3.7 (QH)
/LDR_PWR: J4.5, R21.1, U1.8 (GPIO21)
/LDR_SENSE: R20.1, R21.2, U1.10 (GPIO1)
/LED_B_A: D3.4 (BA), R16.2
/LED_B_DRV: R16.1, U3.6 (QG)
/LED_G_A: D3.3 (GA), R15.2
/LED_G_DRV: R15.1, U3.5 (QF)
/LED_R_A: D3.1 (RA), R14.2
/LED_R_DRV: R14.1, U3.4 (QE)
/MOTOR_N: D2.2 (A), J3.2, Q5.3 (C)
/SCL: J1.3, J4.4, R23.2, U1.5 (GPIO9)
/SDA: J1.2, J4.3, R22.2, U1.4 (GPIO8)
/SEG_A: DS1.11 (a), R1.2
/SEG_B: DS1.7 (b), R2.2
/SEG_C: DS1.4 (c), R3.2
/SEG_D: DS1.2 (d), R4.2
/SEG_DP: DS1.3 (DPX), R8.2
/SEG_E: DS1.1 (e), R5.2
/SEG_F: DS1.10 (f), R6.2
/SEG_G: DS1.5 (g), R7.2
/SR_A: R1.1, U2.15 (QA)
/SR_B: R2.1, U2.1 (QB)
/SR_C: R3.1, U2.2 (QC)
/SR_CHAIN: U2.9 (QH'), U3.14 (SER)
/SR_CLK: U1.3 (GPIO7), U2.11 (SRCLK), U3.11 (SRCLK)
/SR_D: R4.1, U2.3 (QD)
/SR_DATA: U1.2 (GPIO6), U2.14 (SER)
/SR_DP: R8.1, U2.7 (QH)
/SR_E: R5.1, U2.4 (QE)
/SR_F: R6.1, U2.5 (QF)
/SR_G: R7.1, U2.6 (QG)
/SR_LATCH: U1.6 (GPIO10), U2.12 (RCLK), U3.12 (RCLK)
/SR_OE: R17.2, U1.7 (GPIO20), U2.13 (~OE), U3.13 (~OE)
/VBAT: D1.2 (A), J2.2, R18.1
/VBAT_SENSE: C3.1, C4.2, R18.2, R19.1, U1.9 (GPIO0)
/VBUS: D1.1 (K), U1.16 (5V)

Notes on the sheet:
MCU: ESP32-C3 SuperMini (only GPIO0-10, 20, 21 exist)
Segment driver: 74HC595 + 8x 220R
Digit / LED / haptic driver: 74HC595 + NPN low-side switches
Display: 4-digit common cathode
Buttons
Battery sense
Light sensor
Decoupling
RGB LED
Power: Li-Po -> D1 -> 5V pin. TP4056 module (own USB port) on J2
Accessory port
DS3231 RTC module
Haptic motor
Power flags (ERC only)
Mounting holes
U1 pin numbers are the SuperMini's pads, seen from its component side with USB-C at the top: pads 1-8 run DOWN the left edge, pads 9-16 run UP the right edge (counted like a DIP chip). Pad 1 = GPIO5 (the square pad on the PCB), pad 16 = 5V. It is soldered to the BACK of the PCB, components facing a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
U2, U3 (DIP-16): hold the chip with the notch at the top. Pin 1 is top-left, next to the notch (often also marked with a dot). Count DOWN the left side 1-8, then UP the right side 9-16.
DS1 seen from the front with the decimal points at the bottom: pins 1-6 run left to right along the BOTTOM edge, pins 7-12 run right to left along the TOP edge. Top row, left to right: 12 DIG1 11 A 10 F 9 DIG2 8 DIG3 7 B Bottom row, left to right: 1 E 2 D 3 DP 4 C 5 G 6 DIG4
Q1-Q5 (TO-92): flat face towards you, legs pointing down: left = E (1), middle = B (2), right = C (3). PN2222A and 2N3904 are E-B-C. BC547 is C-B-E and must not be used without turning it round.
D3: common cathode. The longest leg is K (2). Leg order: R (1), K (2), G (3), B (4).
D1, D2: the band printed on the body is the cathode (K, pin 1).
J4 from the front, board top edge up: top: 1 GND 3 SDA 5 AUX (3.3 V, awake) bottom: 2 3V3 4 SCL 6 AIN (audio in)
Pins with the same label are connected. Generated from hardware/scripts/design.py - edit that and regenerate.

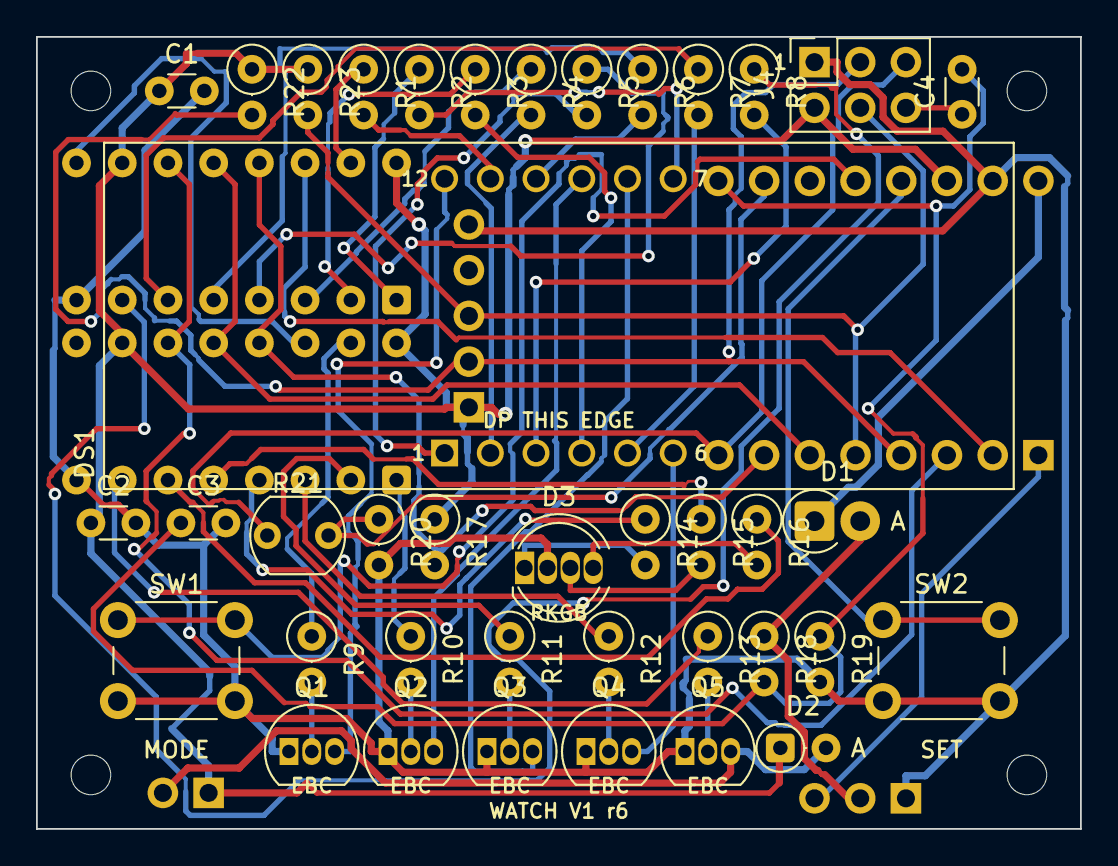
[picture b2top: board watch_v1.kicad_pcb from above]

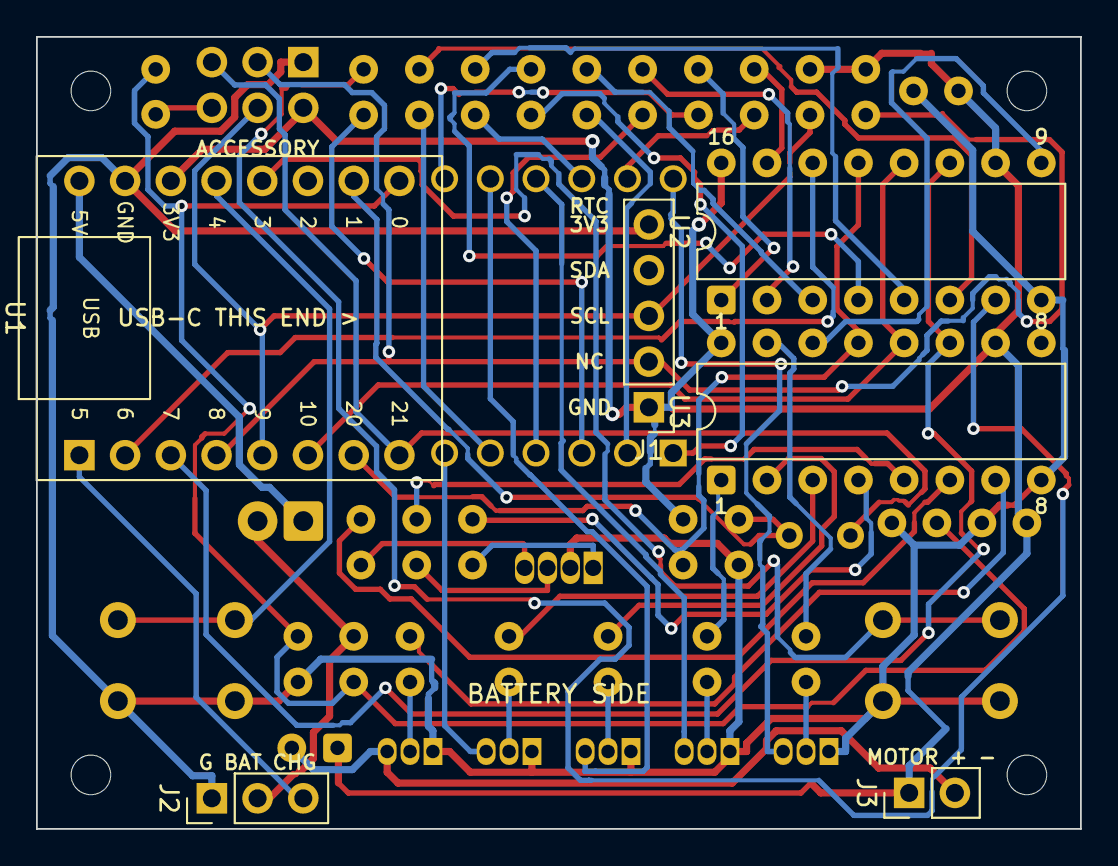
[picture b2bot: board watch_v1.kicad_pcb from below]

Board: 2 copper layers, 58.0 x 44.0 mm, 49 parts (6 on the bottom side), 55 nets.

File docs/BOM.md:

# Parts list

Quantities are for **one watch**. Everything is through-hole and hand-solderable. The reference designators (R1, U2…) match the schematic and the board's printing; the authority is [`hardware/scripts/design.py`](../hardware/scripts/design.py) — if this list and that file ever disagree, the file is right.

Buy a few spares of the cheap parts: resistors and transistors come in strips anyway.

## On the board

| Ref | Qty | Part | Notes |
|---|---|---|---|
| U1 | 1 | ESP32-C3 SuperMini | The processor board, USB-C. Soldered to the **back** of the PCB, USB-C towards the right edge. |
| U2, U3 | 2 | 74HC595 shift register, DIP-16 | Must be the **HC** family (works at 3.3 V). Back of the board. |
| DS1 | 1 | 0.56" 4-digit 7-segment display, **common cathode**, 12 pins | 5643AS / 5641AS / CC56-12. Check "common cathode" — the common-anode twin (5643BS) will not light. |
| Q1–Q5 | 5 | NPN transistor, TO-92, pins E-B-C | PN2222A / 2N2222A (TO-92) / 2N3904. Check the pin order of what you buy: flat side facing you, left to right, must be emitter, base, collector. BC547 is C-B-E and would go in backwards. |
| D1 | 1 | 1N5819 Schottky diode | Battery → processor board |
| D2 | 1 | 1N4148 diode | Protects Q5 from the motor |
| D3 | 1 | 5 mm RGB LED, **common cathode**, 4 legs | Leg order red, cathode (longest), green, blue |
| R1–R8, R14 | 9 | 220 Ω resistor, ¼ W | Display segments, red LED |
| R9–R13 | 5 | 1 kΩ | Transistor bases |
| R15, R16 | 2 | 100 Ω | Green and blue LED |
| R17, R20 | 2 | 10 kΩ | Display-off-at-boot pull-up; light sensor divider |
| R18, R19 | 2 | 100 kΩ | Battery measurement |
| R22, R23 | 2 | 4.7 kΩ | I²C pull-ups |
| R21 | 1 | Photoresistor (LDR) GL5528 | Light sensor |
| C1–C4 | 4 | 100 nF ceramic capacitor, 2.5 mm pitch | |
| SW1, SW2 | 2 | 6 × 6 mm tactile switch, **13 mm tall** | The height matters: the stem has to reach through the lid |
| J4 | 1 | 2×3 female pin socket, 2.54 mm, 8.5 mm tall | Accessory socket |
| — | 1 | Watch V1 PCB, 58 × 44 mm | See [ORDERING.md](ORDERING.md) |

Resistors stand upright (one leg folded over) to save space.

J1, J2 and J3 on the board are rows of solder pads for wires, not connectors to buy.

## Off the board, wired to it

| Qty | Part | Connects to | Notes |
|---|---|---|---|
| 1 | Li-Po cell, 3.7 V, about 150 mAh, about 23 × 15 × 5.5 mm, **with protection circuit** | Charger board B+ / B− | e.g. size "551521". Measure before printing the case — the pocket is 23.4 × 16 mm. |
| 1 | TP4056 charger board **with protection** (the kind with six pads: IN+, IN−, B+, B−, OUT+, OUT−) | J2: GND, BAT, CHG | Its own USB socket is the watch's charging port. USB-C boards are about 28 × 17.5 mm, micro-USB ones 26 × 17 mm — set `charger` in the enclosure file to match. |
| 1 | 12 kΩ resistor, **0805 surface-mount** (or see note) | Replaces the charger board's R<sub>PROG</sub> | **Required.** The board ships set for 1000 mA, far too much for a 150 mAh cell. 12 kΩ gives about 100 mA. |
| 1 | DS3231 real-time-clock module, small type ("DS3231 for Raspberry Pi", about 14 × 14 mm) | J1: 3V3, SDA, SCL, GND | Optional but recommended: without it the watch must re-sync over Wi-Fi every 3 hours to stay accurate. |
| 1 | Coin vibration motor, 10 mm, 3 V | J3: +, − | |
| — | Thin stranded wire | | |

About the charge-current resistor: on the TP4056 board, find the small resistor marked `122` (1.2 kΩ) next to the chip, remove it and fit 12 kΩ (`123`). Charge current = 1200 ÷ kΩ, in mA: 12 kΩ → 100 mA, 15 kΩ → 80 mA. Charging a small cell at the board's default rate overheats it — do not skip this.

## Case and strap

| Qty | Part | Notes |
|---|---|---|
| 1 | Printed base and lid | Clear PETG or clear resin — [ORDERING.md](ORDERING.md) |
| 1 | Printed LED dome and LED spacer | `led_dome.stl` (clear or translucent white) and `led_spacer.stl` (any colour); a few grams together |
| 4 | M2 × 16 mm pan-head screws | Self-tap into the lid; or M2 heat-set inserts and `screw_tap_d = 3.2` |
| 1 | 22 mm one-piece strap (NATO or hook-and-loop) | Threads through both lugs |

## Packs (optional, per teacher)

| Pack | Parts | For |
|---|---|---|
| Environment | BME280 3.3 V I²C breakout, 2×3 male header, perfboard scrap | Temperature, humidity, pressure, logging |
| Sound | MAX4466 microphone amplifier board, 2×3 male header, perfboard scrap | Tuner |

Wiring is in [ADDONS.md](ADDONS.md).

## Tools and consumables

Soldering iron with a fine tip, solder, flush cutters, tweezers, multimeter, USB-C **data** cable, small Phillips screwdriver, a little double-sided foam tape for the battery and charger board.

## Prototyping without the PCB

The whole circuit fits on a breadboard using the same parts and the pin table at the top of [`firmware/watch_v1/config.h`](../firmware/watch_v1/config.h). It is worth building one on a breadboard first to prove the firmware before the boards arrive.

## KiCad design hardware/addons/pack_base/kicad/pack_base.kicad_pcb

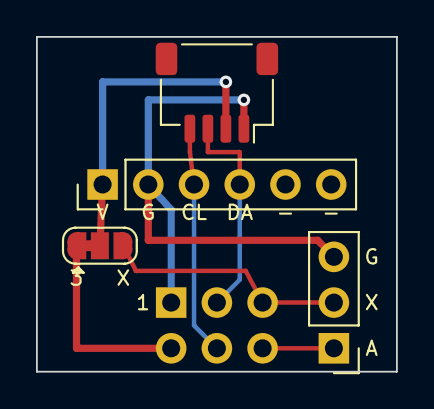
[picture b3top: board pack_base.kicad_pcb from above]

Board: 2 copper layers, 20.0 x 18.6 mm, 5 parts (1 on the bottom side), 7 nets.

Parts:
J1: PinHeader_2x03_P2.54mm_Vertical
J2: PinHeader_1x06_P2.54mm_Vertical
J3: PinHeader_1x03_P2.54mm_Vertical
J5: JST_SH_SM04B-SRSS-TB_1x04-1MP_P1.00mm_Horizontal
JP1: SolderJumper-3_P1.3mm_Bridged12_RoundedPad1.0x1.5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; SolderJumper-3_P1.3mm_Bridged12_RoundedPad1.0x1.5mm

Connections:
+3V3: J1.2, JP1.1
AIN: J1.6, J3.1
AUX: J1.5, J3.2, JP1.3
GND: J1.1, J2.2, J3.3, J5.1
PWR: J2.1, J5.2, JP1.2
SCL: J1.4, J2.3, J5.4
SDA: J1.3, J2.4, J5.3

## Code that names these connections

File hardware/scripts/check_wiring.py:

"""Independent audit of the wiring. Run after gen_sch.py and gen_pcb.py:

    python check_wiring.py

It does not trust design.py. It reads the netlist KiCad itself extracts from
the generated schematic, and the pad nets of the generated board, and checks
them against the pinouts in the parts' datasheets (written out below) and
against what the firmware expects. Anything that disagrees is printed as FAIL.
"""
import json
import os
import re
import shutil
import subprocess
import sys
import tempfile

from sexpr import find, first, parse

HERE = os.path.dirname(os.path.abspath(__file__))
KICAD = os.path.join(HERE, "..", "kicad")
CONFIG_H = os.path.join(HERE, "..", "..", "firmware", "watch_v1", "config.h")
CLI = os.environ.get("KICAD_CLI") or shutil.which("kicad-cli") or os.path.expandvars(
    r"%LOCALAPPDATA%\Programs\KiCad\10.0\bin\kicad-cli.exe")

# ---- datasheet pinouts ------------------------------------------------------
# ESP32-C3 SuperMini, component side up, USB-C at the top. Pads numbered like a DIP.
SUPERMINI = {1: "GPIO5", 2: "GPIO6", 3: "GPIO7", 4: "GPIO8", 5: "GPIO9", 6: "GPIO10", 7: "GPIO20", 8: "GPIO21",
             9: "GPIO0", 10: "GPIO1", 11: "GPIO2", 12: "GPIO3", 13: "GPIO4", 14: "3V3", 15: "GND", 16: "5V"}
# 74HC595: outputs QA..QH, then the control pins.
HC595_Q = {"QA": 15, "QB": 1, "QC": 2, "QD": 3, "QE": 4, "QF": 5, "QG": 6, "QH": 7}
HC595 = {"SER": 14, "SRCLK": 11, "RCLK": 12, "OE": 13, "SRCLR": 10, "VCC": 16, "GND": 8, "QH'": 9}
# 5641AS / 5643AS / CC56-12 four-digit common-cathode display.
DISPLAY = {"A": 11, "B": 7, "C": 4, "D": 2, "E": 1, "F": 10, "G": 5, "DP": 3, "DIG1": 12, "DIG2": 9, "DIG3": 8, "DIG4": 6}

failures = 0


def check(ok, text):
    global failures
    print(("  ok    " if ok else "  FAIL  ") + text)
    failures += not ok


def schematic_nets():
    """{net name: {(ref, pin)}} as KiCad extracts it from the schematic."""
    out_file = os.path.join(tempfile.mkdtemp(), "watch_v1.net")
    subprocess.run([CLI, "sch", "export", "netlist", "--format", "kicadsexpr", "-o", out_file,
                    os.path.join(KICAD, "watch_v1.kicad_sch")], check=True, stdout=subprocess.DEVNULL)
    tree = parse(open(out_file, encoding="utf-8").read())
    nets = {}
    for net in find(first(tree, "nets"), "net"):
        name = first(net, "name")[1].lstrip("/")
        nets[name] = {(first(n, "ref")[1], first(n, "pin")[1]) for n in find(net, "node")}
    return nets


def main():
    nets = schematic_nets()
    where = {}                                        # (ref, pin) -> net
    for name, nodes in nets.items():
        for node in nodes:
            where[node] = name

    def net(ref, pin):
        return where.get((ref, str(pin)), "(not connected)")

    def joined(a, b):
        return net(*a) == net(*b) and not net(*a).startswith("unconnected") and net(*a) != "(not connected)"

    def through(a, part, b):
        """a - [two-pin part] - b: the part sits between the two points."""
        ends = {net(part, 1), net(part, 2)}
        return ends == {net(*a), net(*b)} and len(ends) == 2

    print("Firmware pins (config.h) against the SuperMini pads")
    gpio_pad = {int(v[4:]): k for k, v in SUPERMINI.items() if v.startswith("GPIO")}
    pins = dict(re.findall(r"#define\s+(PIN_\w+)\s+(\d+)", open(CONFIG_H, encoding="utf-8").read()))
    expected = {"PIN_VBAT_SENSE": "VBAT_SENSE", "PIN_LDR_SENSE": "LDR_SENSE", "PIN_BTN_MODE": "BTN_MODE",
                "PIN_BTN_SET": "BTN_SET", "PIN_CHRG": "CHRG", "PIN_SR_DATA": "SR_DATA", "PIN_SR_CLK": "SR_CLK",
                "PIN_SDA": "SDA", "PIN_SCL": "SCL", "PIN_SR_LATCH": "SR_LATCH", "PIN_SR_OE": "SR_OE",
                "PIN_LDR_PWR": "LDR_PWR"}
    for define, want in expected.items():
        gpio = int(pins[define])
        check(net("U1", gpio_pad[gpio]) == want, f"{define} = GPIO{gpio} = U1 pad {gpio_pad[gpio]} is on net {want}")
    check(net("U1", 11).startswith("unconnected"), "GPIO2 (boot strapping pin) is left unconnected")
    check(net("U1", 14) == "+3V3" and net("U1", 15) == "GND" and net("U1", 16) == "VBUS", "U1 power pads: 3V3, GND, 5V")

    print("Shift registers")
    for u in ("U2", "U3"):
        check(net(u, HC595["SRCLK"]) == "SR_CLK" and net(u, HC595["RCLK"]) == "SR_LATCH" and net(u, HC595["OE"]) == "SR_OE",
              f"{u} clock, latch and output-enable are on the shared lines")
        check(net(u, HC595["VCC"]) == "+3V3" and net(u, HC595["GND"]) == "GND" and net(u, HC595["SRCLR"]) == "+3V3",
              f"{u} powered, and its clear pin is tied high")
    check(net("U2", HC595["SER"]) == "SR_DATA", "U2 data in comes from the processor")
    check(joined(("U2", HC595["QH'"]), ("U3", HC595["SER"])), "U2 serial out feeds U3 data in (daisy chain)")
    check(through(("U1", gpio_pad[20]), "R17", ("U1", 14)), "R17 pulls output-enable up to 3V3 (display off until the firmware runs)")

    print("Display segments: U2 output -> 220 ohm -> display pin   (firmware bit order a..g, dp = QA..QH)")
    for i, (seg, q) in enumerate(zip(["A", "B", "C", "D", "E", "F", "G", "DP"], HC595_Q)):
        check(through(("U2", HC595_Q[q]), f"R{i + 1}", ("DS1", DISPLAY[seg])),
              f"segment {seg:2s}: U2 {q} (pin {HC595_Q[q]}) - R{i + 1} - DS1 pin {DISPLAY[seg]}")

    print("Display digits: U3 output -> 1k -> transistor base; emitter to ground; collector to the digit's cathode")
    for i, q in enumerate(["QA", "QB", "QC", "QD"]):
        tr = f"Q{i + 1}"
        check(through(("U3", HC595_Q[q]), f"R{9 + i}", (tr, 2)) and net(tr, 1) == "GND" and
              joined((tr, 3), ("DS1", DISPLAY[f"DIG{i + 1}"])),
              f"digit {i + 1}: U3 {q} (pin {HC595_Q[q]}) - R{9 + i} - {tr} base; {tr} collector - DS1 pin {DISPLAY[f'DIG{i + 1}']}")

    print("RGB LED and vibration motor on U3 (firmware: QE red, QF green, QG blue, QH motor)")
    for q, r, leg, colour in (("QE", "R14", 1, "red"), ("QF", "R15", 3, "green"), ("QG", "R16", 4, "blue")):
        check(through(("U3", HC595_Q[q]), r, ("D3", leg)), f"{colour}: U3 {q} - {r} - D3 leg {leg}")
    check(net("D3", 2) == "GND", "D3 common cathode (leg 2) to ground")
    check(through(("U3", HC595_Q["QH"]), "R13", ("Q5", 2)) and net("Q5", 1) == "GND", "motor: U3 QH - R13 - Q5 base, emitter to ground")
    check(net("J3", 1) == "+3V3" and joined(("J3", 2), ("Q5", 3)), "motor between 3V3 (J3 +) and Q5 collector (J3 -)")
    check(net("D2", 1) == "+3V3" and joined(("D2", 2), ("Q5", 3)), "D2 across the motor, cathode to 3V3 (flyback)")

    print("Power")
    check(net("D1", 1) == "VBUS" and net("D1", 2) == "VBAT", "D1: anode on the battery, cathode on the SuperMini 5V pin")
    check(net("J2", 1) == "GND" and net("J2", 2) == "VBAT" and net("J2", 3) == "CHRG", "J2 charger pads: GND, battery, charge signal")
    check(nets["VBUS"] == {("U1", "16"), ("D1", "1")}, "nothing but D1 touches the USB 5V pin (the charger is separate)")
    check(through(("J2", 2), "R18", ("U1", gpio_pad[0])) and through(("U1", gpio_pad[0]), "R19", ("U1", 15)),
          "battery sense: battery - R18 - GPIO0 - R19 - ground")
    for c in ("C1", "C2"):
        check({net(c, 1), net(c, 2)} == {"+3V3", "GND"}, f"{c} decouples 3V3")

    print("Buttons, light sensor, I2C, accessory socket")
    for sw, name in (("SW1", "BTN_MODE"), ("SW2", "BTN_SET")):
        check({net(sw, 1), net(sw, 2)} == {name, "GND"}, f"{sw} between {name} and ground")
    check(through(("U1", gpio_pad[21]), "R21", ("U1", gpio_pad[1])) and through(("U1", gpio_pad[1]), "R20", ("U1", 15)),
          "light sensor: GPIO21 - LDR - GPIO1 - R20 - ground")
    check(through(("U1", gpio_pad[8]), "R22", ("U1", 14)) and through(("U1", gpio_pad[9]), "R23", ("U1", 14)),
          "I2C pull-ups R22 (SDA) and R23 (SCL) to 3V3")
    check([net("J1", n) for n in (1, 2, 3, 5)] == ["+3V3", "SDA", "SCL", "GND"], "J1 clock module pads: 3V3, SDA, SCL, -, GND")
    check([net("J4", n) for n in range(1, 7)] == ["GND", "+3V3", "SDA", "SCL", "LDR_PWR", "AIN"],
          "J4 accessory socket: 1 GND, 2 3V3, 3 SDA, 4 SCL, 5 AUX, 6 AIN")
    check(through(("J4", 6), "C4", ("U1", gpio_pad[0])), "C4 couples AIN onto the battery-sense pin")

    print("Board against schematic")
    with open(os.path.join(KICAD, "watch_v1.pads.json"), encoding="utf-8") as f:
        pads = json.load(f)["pads"]
    board = {}
    for p in pads:
        if p["net"]:
            board.setdefault(p["net"], set()).add((p["ref"], p["num"]))
    schematic = {k: v for k, v in nets.items() if not k.startswith("unconnected")}
    check(board == schematic, f"every pad on the board is on the same net as in the schematic ({len(schematic)} nets)")
    check(all(len(v) >= 2 for v in schematic.values()), "no net has only one pin")

    print(f"\n{'ALL CHECKS PASSED' if not failures else str(failures) + ' CHECK(S) FAILED'}")
    return 1 if failures else 0


if __name__ == "__main__":
    sys.exit(main())
